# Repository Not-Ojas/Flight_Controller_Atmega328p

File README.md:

# Flight_Controller_Atmega328p
A Bare Metal Flight Controller using Atmega328p or the Arduino Nano.

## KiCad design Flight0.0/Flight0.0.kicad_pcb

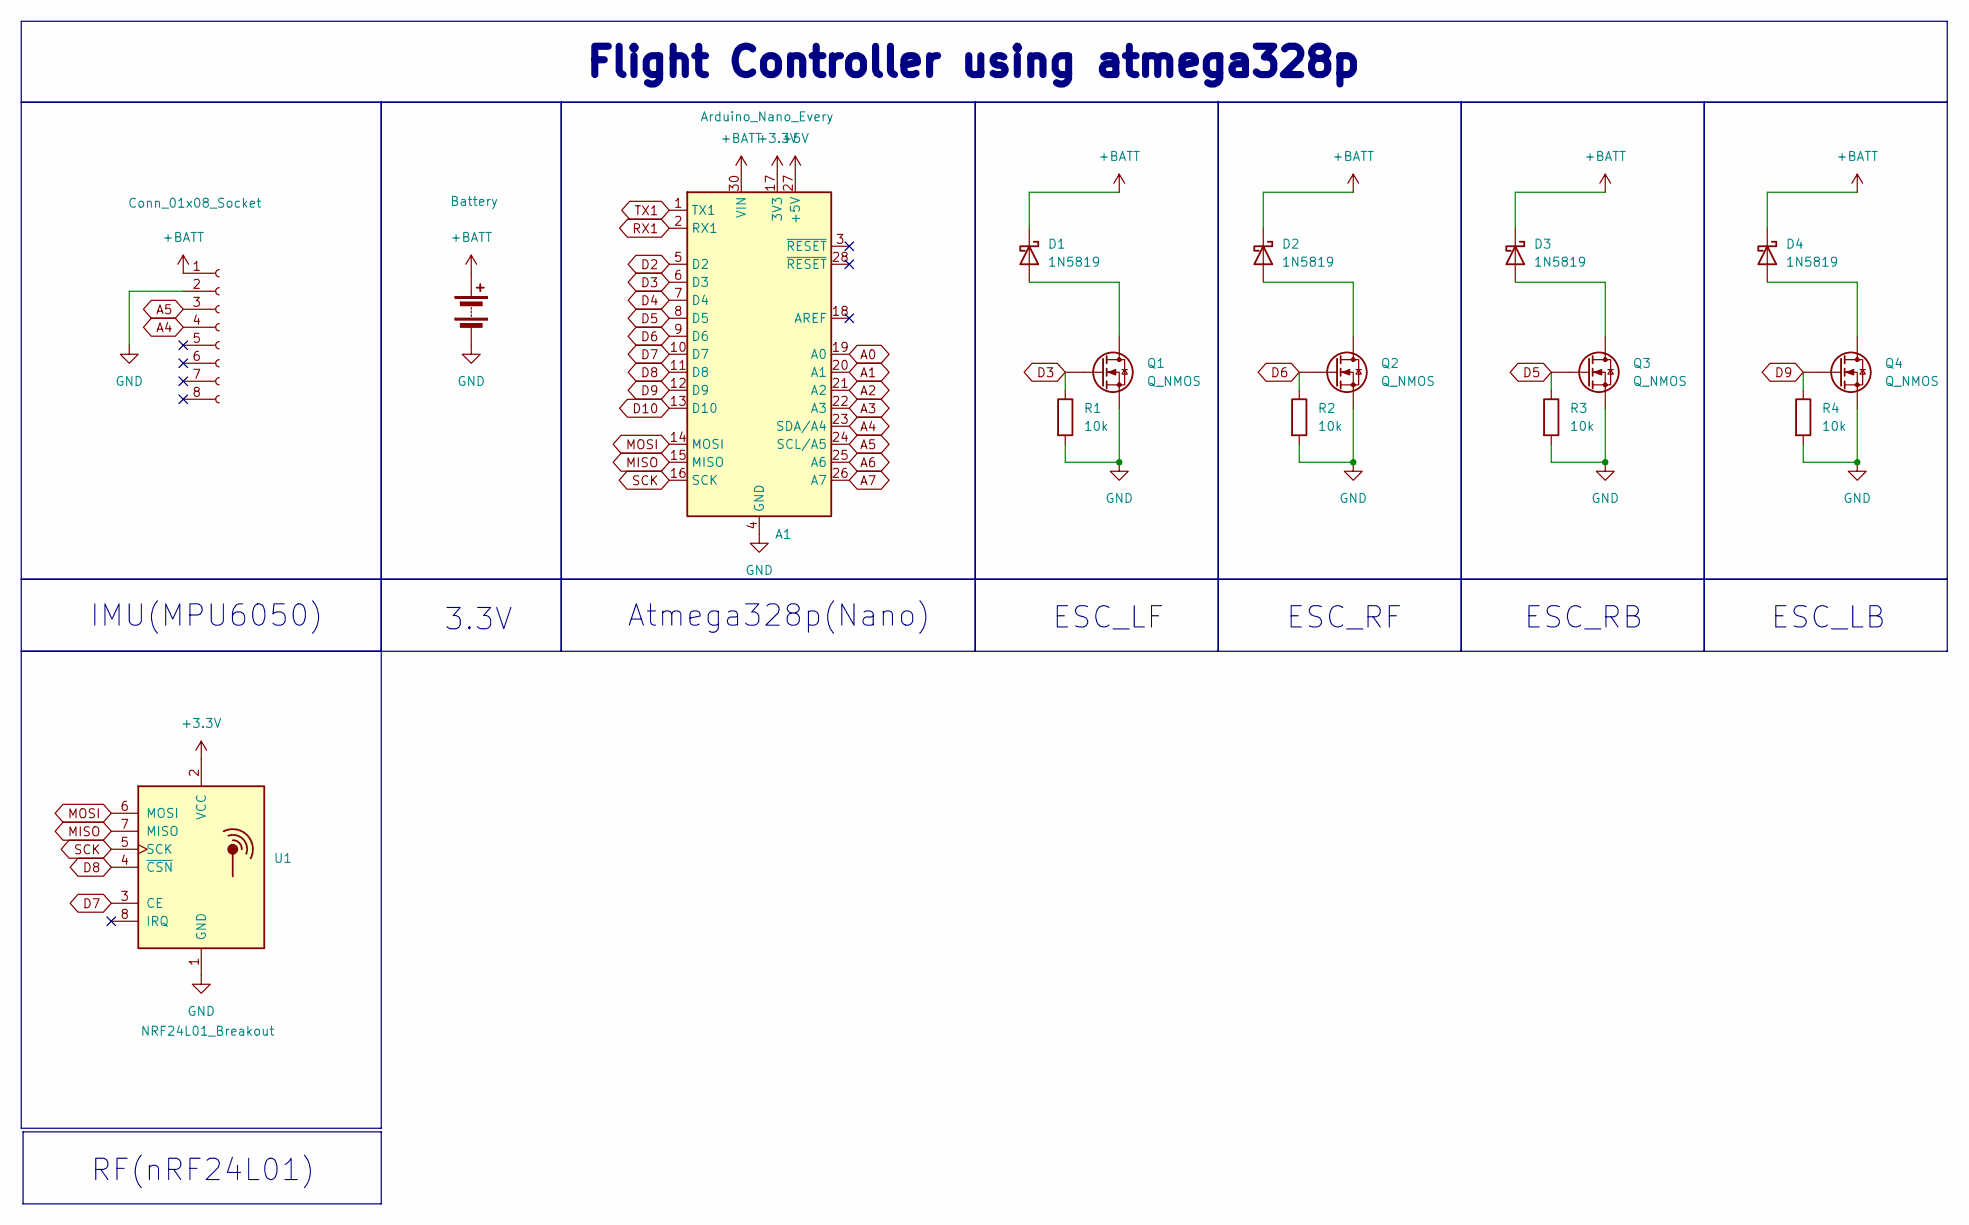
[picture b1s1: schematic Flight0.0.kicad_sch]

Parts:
A1: Arduino_Nano_Every; Arduino_Nano
BT1: Battery; PinHeader_1x02_P2.54mm_Vertical
D1, D2, D3, D4: 1N5819; D_DO-41_SOD81_P10.16mm_Horizontal
J1: Conn_01x08_Socket; PinHeader_1x08_P2.54mm_Vertical
Q1, Q2, Q3, Q4: Q_NMOS; SI2302
R1, R2, R3, R4: 10k; R_1206_3216Metric
U1: NRF24L01_Breakout; nRF24L01_Breakout

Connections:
+3.3V: A1.17 (3V3), U1.2 (VCC)
+5V: A1.27 (+5V)
+BATT: A1.30 (VIN), BT1.1 (+), D1.1 (K), D2.1 (K), D3.1 (K), D4.1 (K), J1.1
A0: A1.19 (A0)
A1: A1.20 (A1)
A2: A1.21 (A2)
A3: A1.22 (A3)
A4: A1.23 (SDA/A4), J1.4
A5: A1.24 (SCL/A5), J1.3
A6: A1.25 (A6)
A7: A1.26 (A7)
D2: A1.5 (D2)
D3: A1.6 (D3), Q1.G, R1.1
D4: A1.7 (D4)
D5: A1.8 (D5), Q3.G, R3.1
D6: A1.9 (D6), Q2.G, R2.1
D7: A1.10 (D7), U1.3 (CE)
D8: A1.11 (D8), U1.4 (~CSN)
D9: A1.12 (D9), Q4.G, R4.1
D10: A1.13 (D10)
GND: A1.4 (GND), A1.29 (GND), BT1.2 (-), J1.2, Q1.S, Q2.S, Q3.S, Q4.S, R1.2, R2.2, R3.2, R4.2, U1.1 (GND)
MISO: A1.15 (MISO), U1.7 (MISO)
MOSI: A1.14 (MOSI), U1.6 (MOSI)
unnamed: D1.2 (A), Q1.D
unnamed: D2.2 (A), Q2.D
unnamed: D3.2 (A), Q3.D
unnamed: D4.2 (A), Q4.D
RX1: A1.2 (RX1)
SCK: A1.16 (SCK), U1.5 (SCK)
TX1: A1.1 (TX1)

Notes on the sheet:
ESC_LB
3.3V
Atmega328p(Nano)
Flight Controller using atmega328p
ESC_RB
RF(nRF24L01)
IMU(MPU6050)
ESC_LF
ESC_RF

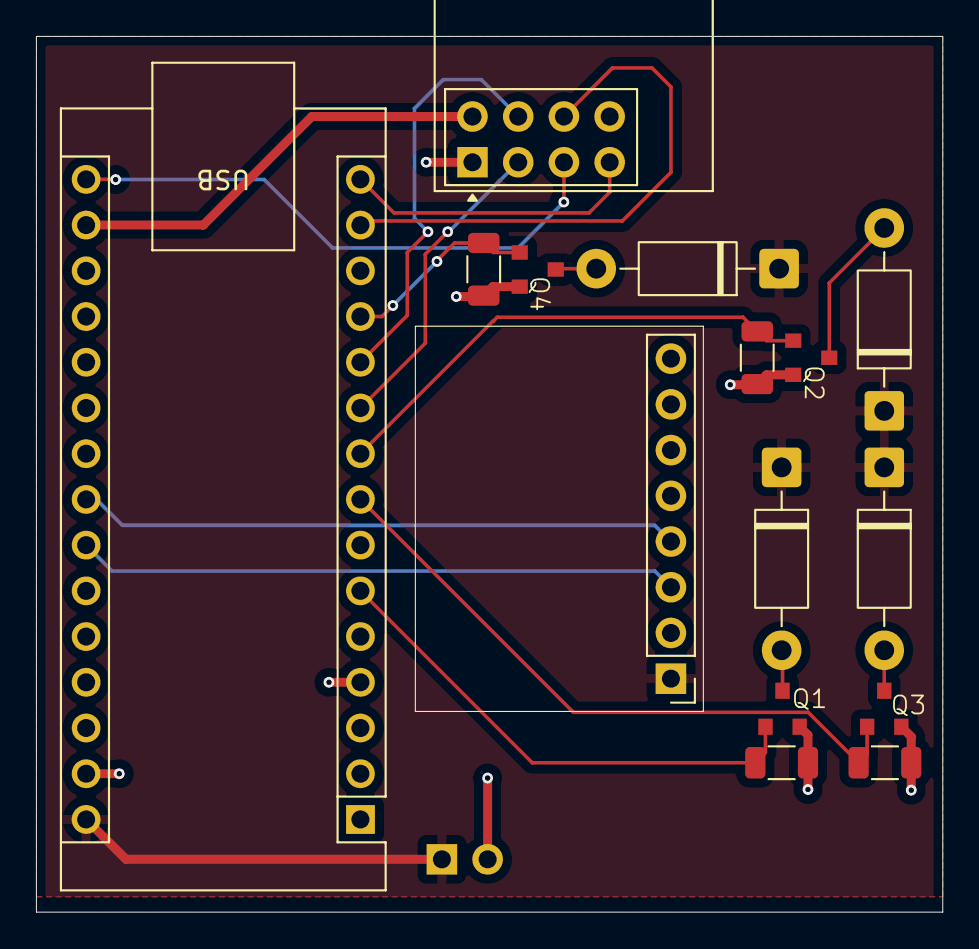
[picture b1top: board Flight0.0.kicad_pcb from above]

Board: 2 copper layers, 50.3 x 48.7 mm, 16 parts (1 on the bottom side), 18 nets.
